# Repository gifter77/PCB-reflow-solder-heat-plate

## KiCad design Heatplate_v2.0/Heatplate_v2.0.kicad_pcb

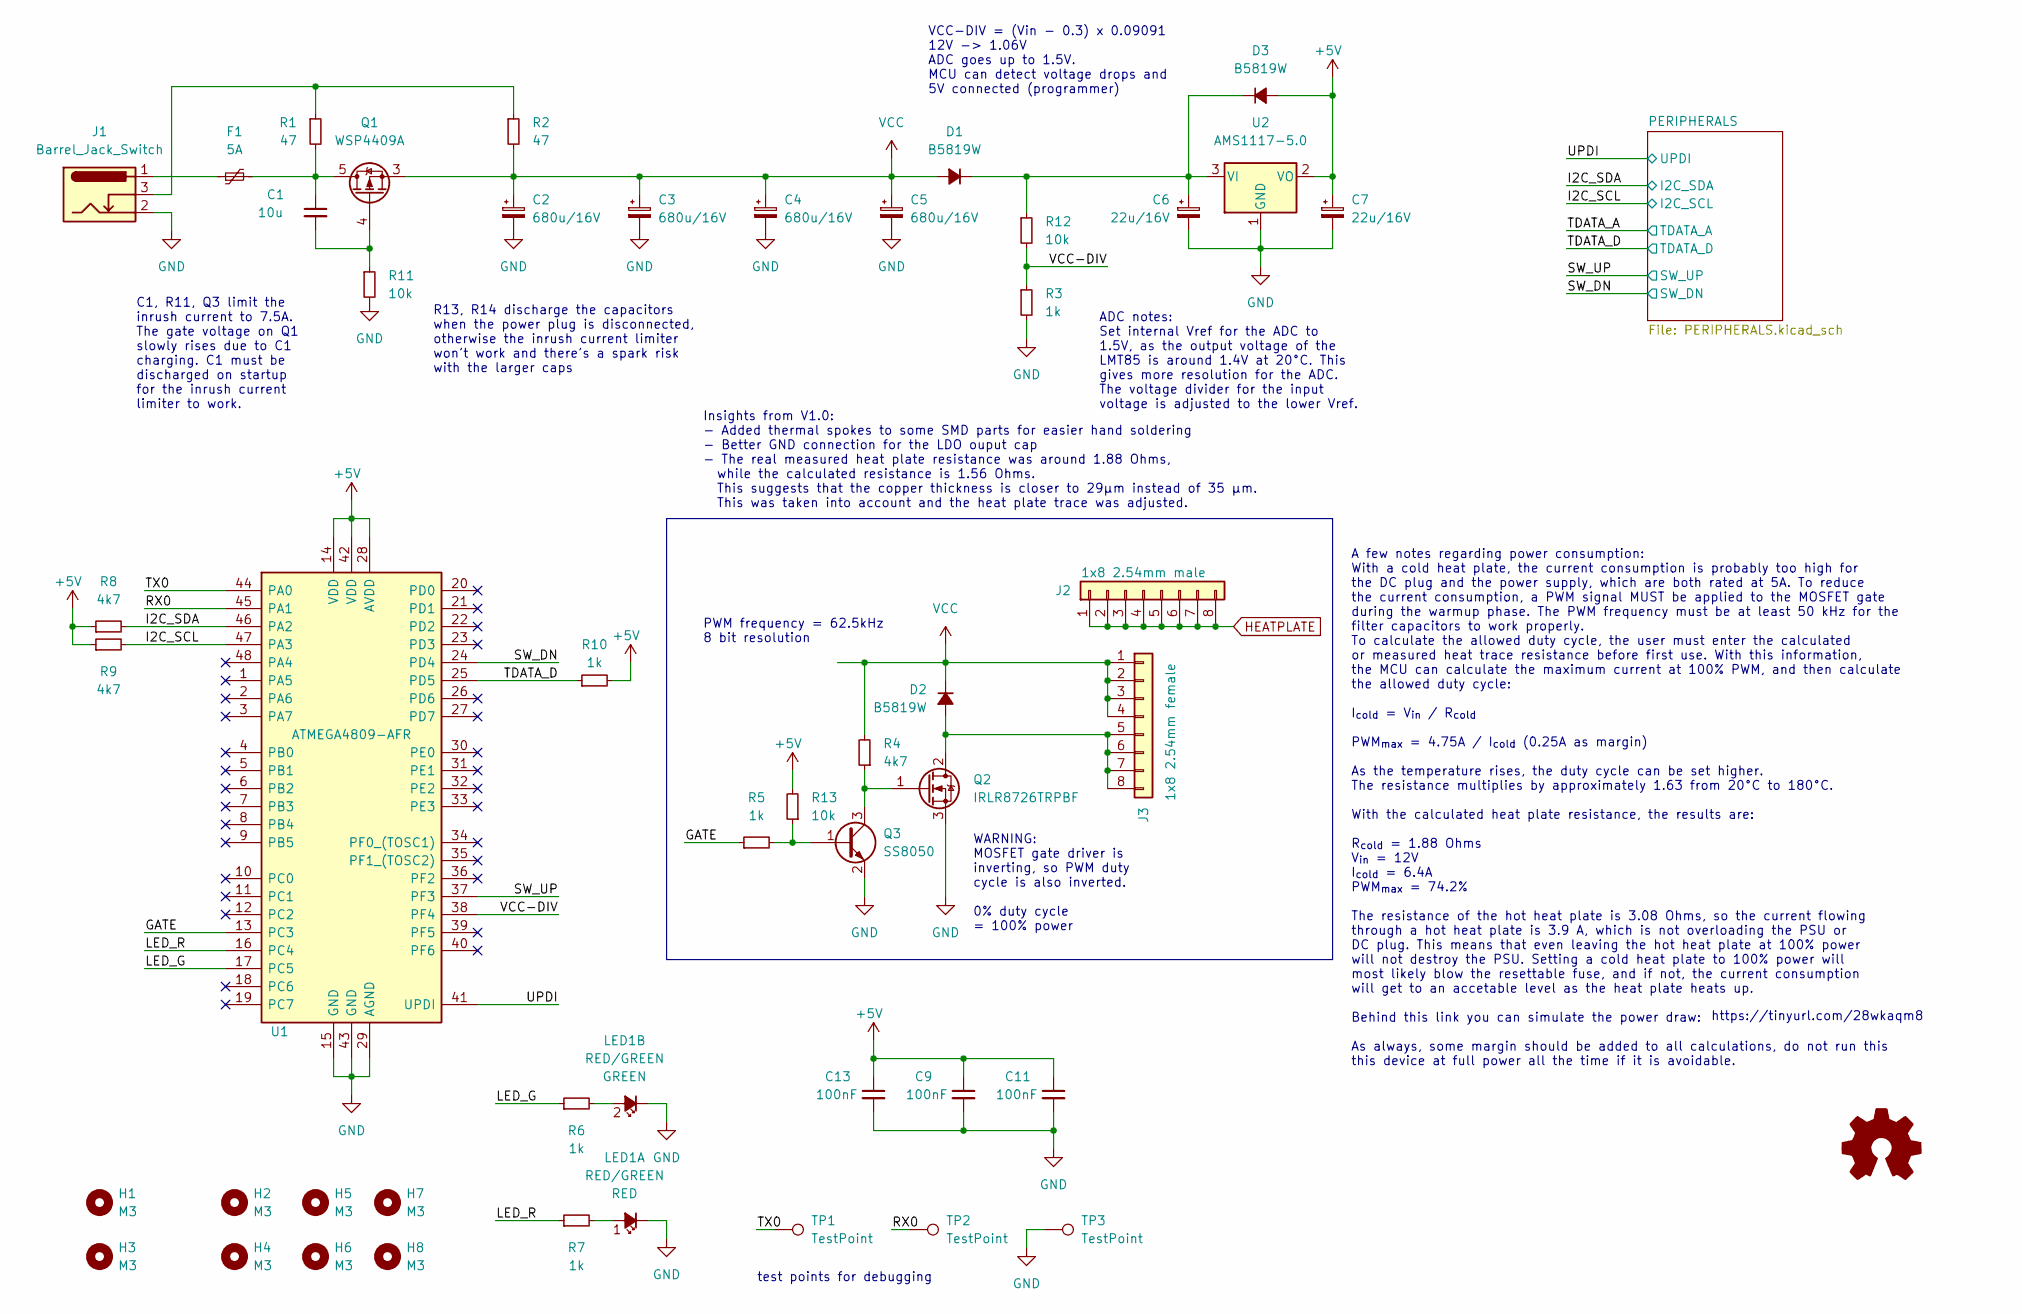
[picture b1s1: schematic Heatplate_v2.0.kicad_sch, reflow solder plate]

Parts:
C1: 10u; C_0805_2012Metric; LCSC Part Number C2922480
C2, C3, C4, C5: 680u/16V; CP_Radial_D8.0mm_P3.50mm; LCSC Part Number C88760
C6, C7: 22u/16V; CP_Elec_4x5.4; LCSC Part Number C88799
C9, C11, C13: 100nF; C_0805_2012Metric; LCSC Part Number C1711
D1, D2, D3: B5819W; D_SOD-123; LCSC Part Number C64885
F1: 5A; Fuse_2920_7451Metric; LCSC Part Number C910846
H1, H2, H3, H4, H5, H6, H7, H8: M3; MountingHole_3.2mm_M3; LCSC Part Number C551332
J1: Barrel_Jack_Switch; BarrelJack_Horizontal; LCSC Part Number C381115
J2: 1x8 2.54mm male; PinHeader_1x08_P2.54mm_Horizontal; LCSC Part Number C2905427
J3: 1x8 2.54mm female; PinSocket_1x08_P2.54mm_Horizontal; LCSC Part Number C2932682
LED1: RED/GREEN; LED_Avago_PLCC4_3.2x2.8mm_CW; LCSC Part Number C131251
LOGO1: Logo_Open_Hardware_Small; OSHW-Logo2_7.3x6mm_SilkScreen
Q1: WSP4409A; SOIC-8_3.9x4.9mm_P1.27mm; LCSC Part Number C2880527
Q2: IRLR8726TRPBF; TO-252-2; LCSC Part Number C81137
Q3: SS8050; SOT-23; LCSC Part Number C444722
R1, R2: 47; R_0805_2012Metric; LCSC Part Number C17714
R3, R5, R6, R7: 1k; R_0805_2012Metric; LCSC Part Number C17513
R4, R8, R9: 4k7; R_0805_2012Metric; LCSC Part Number C17673
R10: 1k; R_0805_2012Metric; LCSC Part Number C17673
R11, R12, R13: 10k; R_0805_2012Metric; LCSC Part Number C17414
TP1, TP2, TP3: TestPoint; TestPoint_Pad_D1.5mm
U1: ATMEGA4809-AFR; TQFP-48_7x7mm_P0.5mm; Manufacturer_Part_Number ATMEGA4809-AFR; Mouser Part Number 556-ATMEGA4809-AFR
U2: AMS1117-5.0; SOT-89-3; LCSC Part Number C351450

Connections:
+5V: C7.1, C9.1, C11.1, C13.1, D3.2 (A), R8.1, R9.1, R10.2, R13.2, U1.14 (VDD), U1.28 (AVDD), U1.42 (VDD), U2.2 (VO); also elsewhere on the board
/GATE: R5.1, U1.13 (PC3)
/I2C_SCL: R9.2, U1.47 (PA3); also elsewhere on the board
/I2C_SDA: R8.2, U1.46 (PA2); also elsewhere on the board
/LED_G: R6.1, U1.17 (PC5)
/LED_R: R7.1, U1.16 (PC4)
/RX0: TP2.1, U1.45 (PA1)
/SW_DN: U1.24 (PD4); also elsewhere on the board
/SW_UP: U1.37 (PF3); also elsewhere on the board
/TDATA_D: R10.1, U1.25 (PD5); also elsewhere on the board
/TX0: TP1.1, U1.44 (PA0)
/UPDI: U1.41 (UPDI); also elsewhere on the board
/VCC-DIV: R3.1, R12.2, U1.38 (PF4)
GND: C2.2, C3.2, C4.2, C5.2, C6.2, C7.2, C9.2, C11.2, C13.2, J1.2, LED1.2 (K1), LED1.4 (K2), Q2.3 (S), Q3.2 (E), R3.2, R11.2, TP3.1, U1.15 (GND), U1.29 (AGND), U1.43 (GND), U2.1 (GND); also elsewhere on the board
unnamed: C1.1, F1.2, Q1.5 (D), Q1.6 (D), Q1.7 (D), Q1.8 (D), R1.2
unnamed: C6.1, D1.1 (K), D3.1 (K), R12.1, U2.3 (VI)
unnamed 17: D2.2 (A), Q2.2 (D); also elsewhere on the board
unnamed: F1.1, J1.1
unnamed: J1.3, R1.1, R2.1
unnamed: LED1.1 (A1), R7.2
unnamed: LED1.3 (A2), R6.2
unnamed: C1.2, Q1.4 (G), R11.1
unnamed: Q2.1 (G), Q3.3 (C), R4.1
unnamed: Q3.1 (B), R5.2, R13.1
VCC: C2.1, C3.1, C4.1, C5.1, D1.2 (A), D2.1 (K), Q1.1 (S), Q1.2 (S), Q1.3 (S), R2.2, R4.2; also elsewhere on the board

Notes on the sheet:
C1, R11, Q3 limit the inrush current to 7.5A. The gate voltage on Q1 slowly rises due to C1 charging. C1 must be discharged on startup for the inrush current limiter to work.
VCC-DIV = (Vin - 0.3) x 0.09091 12V -> 1.06V ADC goes up to 1.5V. MCU can detect voltage drops and 5V connected (programmer)
PWM frequency = 62.5kHz 8 bit resolution
A few notes regarding power consumption: With a cold heat plate, the current consumption is probably too high for the DC plug and the power supply, which are both rated at 5A. To reduce the current consumption, a PWM signal MUST be applied to the MOSFET gate during the warmup phase. The PWM frequen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
WARNING: MOSFET gate driver is inverting, so PWM duty cycle is also inverted. 0% duty cycle = 100% power
R13, R14 discharge the capacitors when the power plug is disconnected, otherwise the inrush current limiter won't work and there's a spark risk with the larger caps
https://tinyurl.com/28wkaqm8
test points for debugging
ADC notes: Set internal Vref for the ADC to 1.5V, as the output voltage of the LMT85 is around 1.4V at 20°C. This gives more resolution for the ADC. The voltage divider for the input voltage is adjusted to the lower Vref.
Insights from V1.0: - Added thermal spokes to some SMD parts for easier hand soldering - Better GND connection for the LDO ouput cap - The real measured heat plate resistance was around 1.88 Ohms, while the calculated resistance is 1.56 Ohms. This suggests that the copper thickness is closer to 29µ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

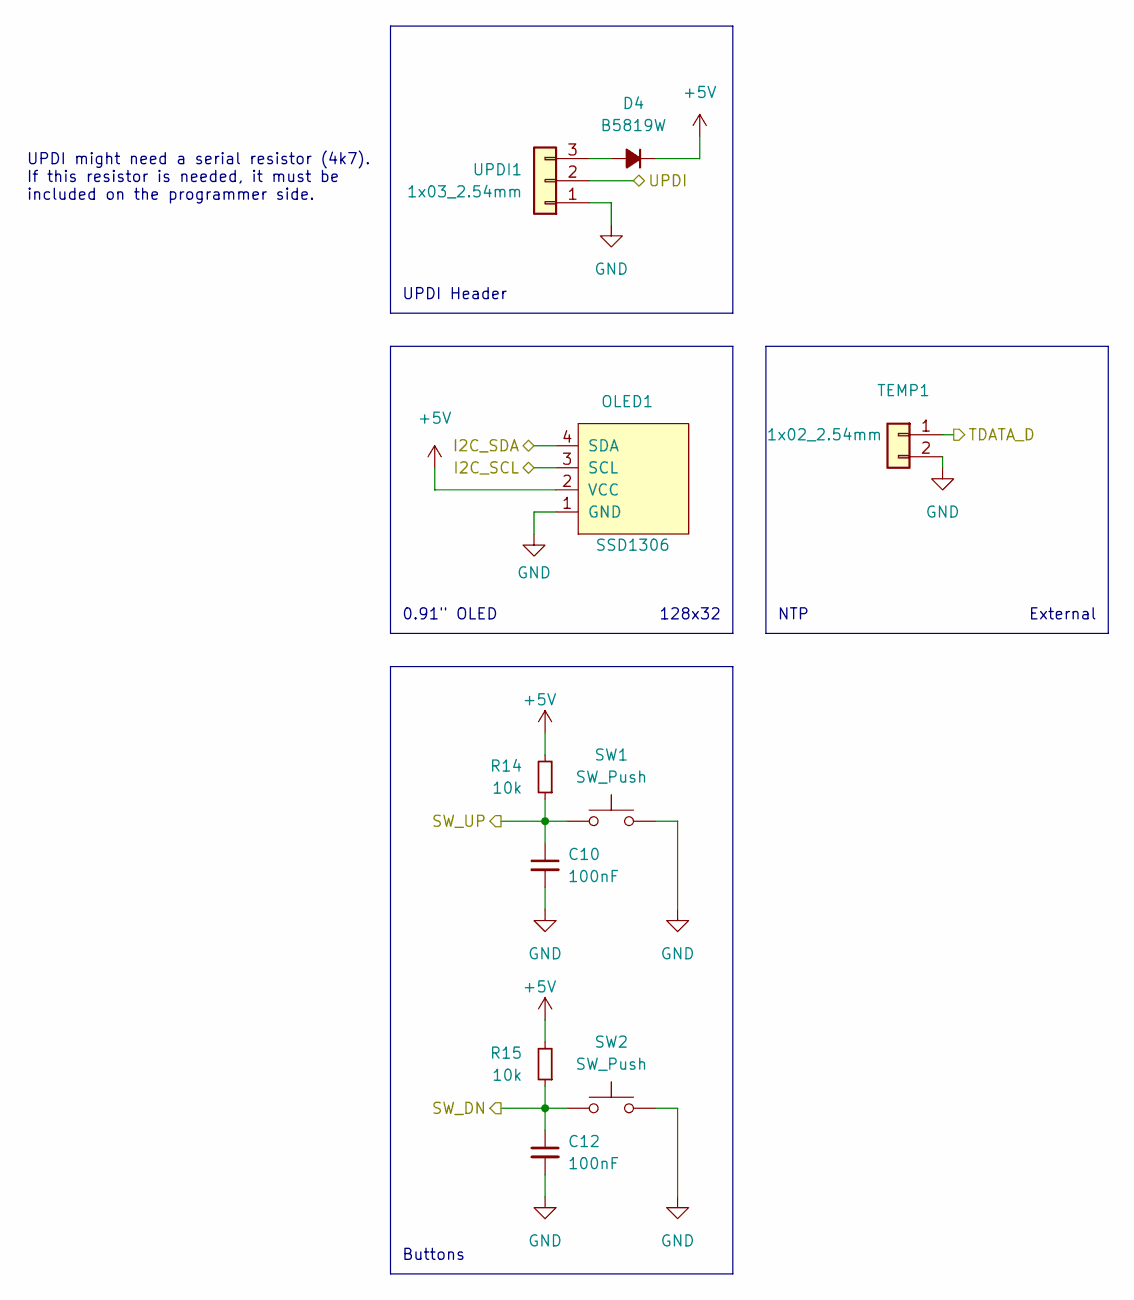
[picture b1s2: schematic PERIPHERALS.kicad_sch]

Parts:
C10, C12: 100nF; C_0805_2012Metric; LCSC Part Number C1711
D4: B5819W; D_SOD-123; LCSC Part Number C64885
OLED1: SSD1306; 0.91Inch-OLED-Module; LCSC Part Number C2718488
R14, R15: 10k; R_0805_2012Metric; LCSC Part Number C17414
SW1, SW2: SW_Push; SW_PUSH_6mm; LCSC Part Number C136682
TEMP1: 1x02_2.54mm; PinHeader_1x02_P2.54mm_Vertical; LCSC Part Number C2905434
UPDI1: 1x03_2.54mm; PinHeader_1x03_P2.54mm_Vertical; LCSC Part Number C49257

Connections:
+5V: D4.1 (K), OLED1.2 (VCC), R14.2, R15.2; also elsewhere on the board
/I2C_SCL: OLED1.3 (SCL); also elsewhere on the board
/I2C_SDA: OLED1.4 (SDA); also elsewhere on the board
/SW_DN: C12.1, R15.1, SW2.1; also elsewhere on the board
/SW_UP: C10.1, R14.1, SW1.1; also elsewhere on the board
/TDATA_D: TEMP1.1; also elsewhere on the board
/UPDI: UPDI1.2; also elsewhere on the board
GND: C10.2, C12.2, OLED1.1 (GND), SW1.2, SW2.2, TEMP1.2, UPDI1.1; also elsewhere on the board
unnamed: D4.2 (A), UPDI1.3

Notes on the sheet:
NTP
UPDI Header
128x32
0.91" OLED
Buttons
UPDI might need a serial resistor (4k7). If this resistor is needed, it must be included on the programmer side.
External

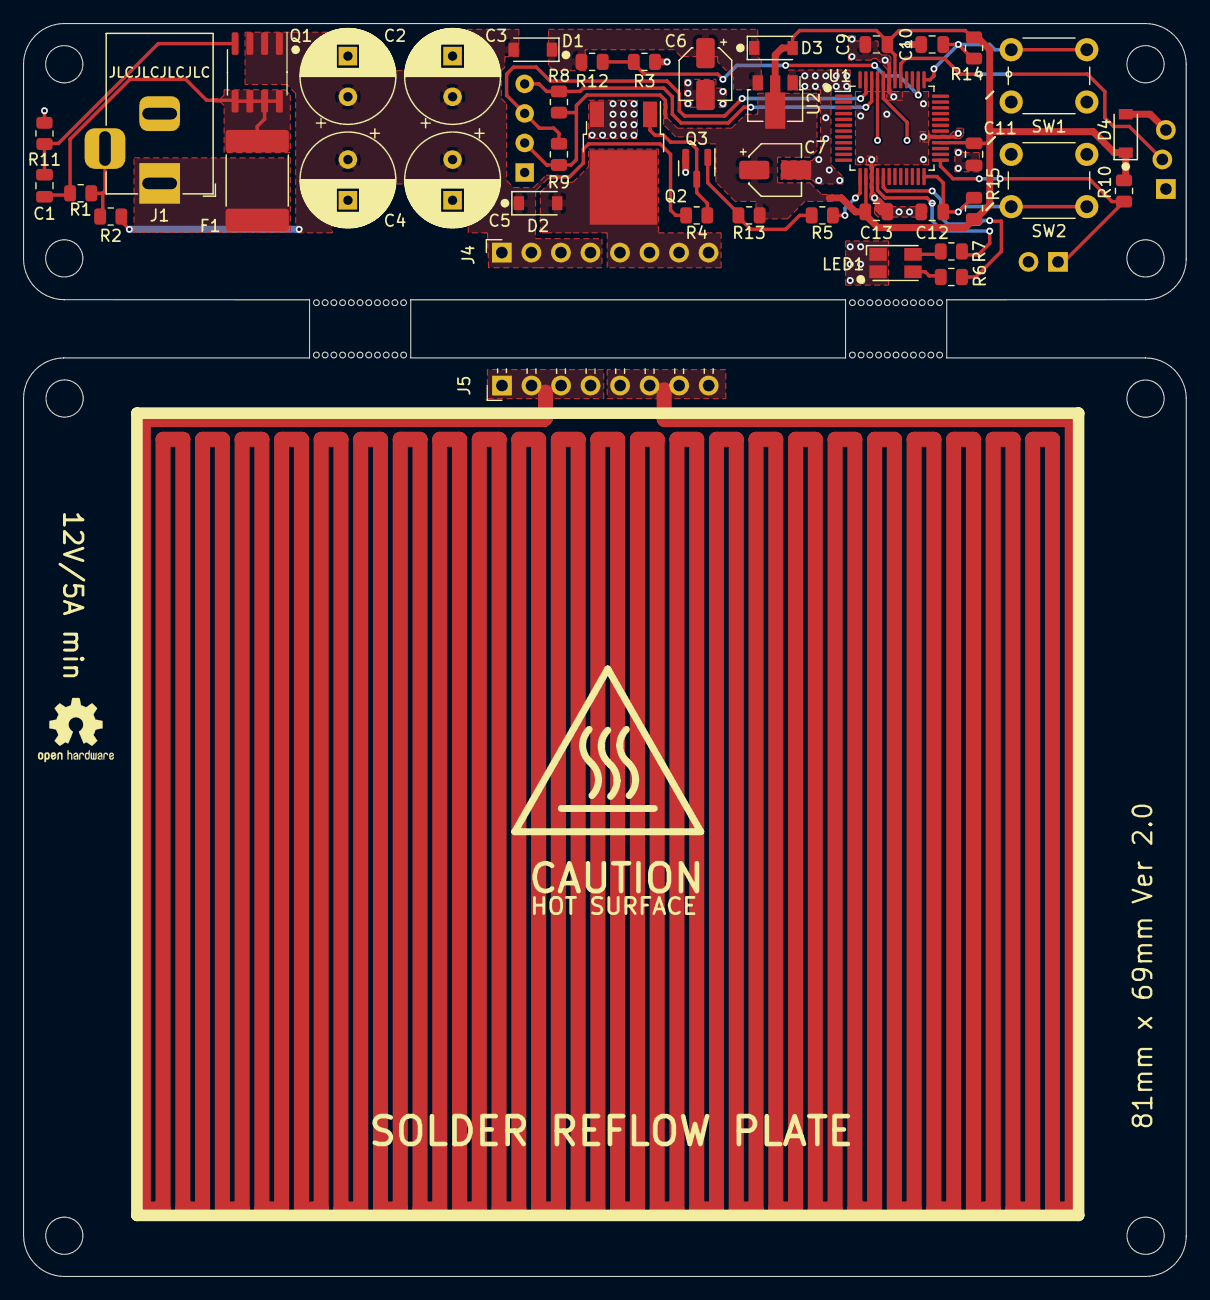
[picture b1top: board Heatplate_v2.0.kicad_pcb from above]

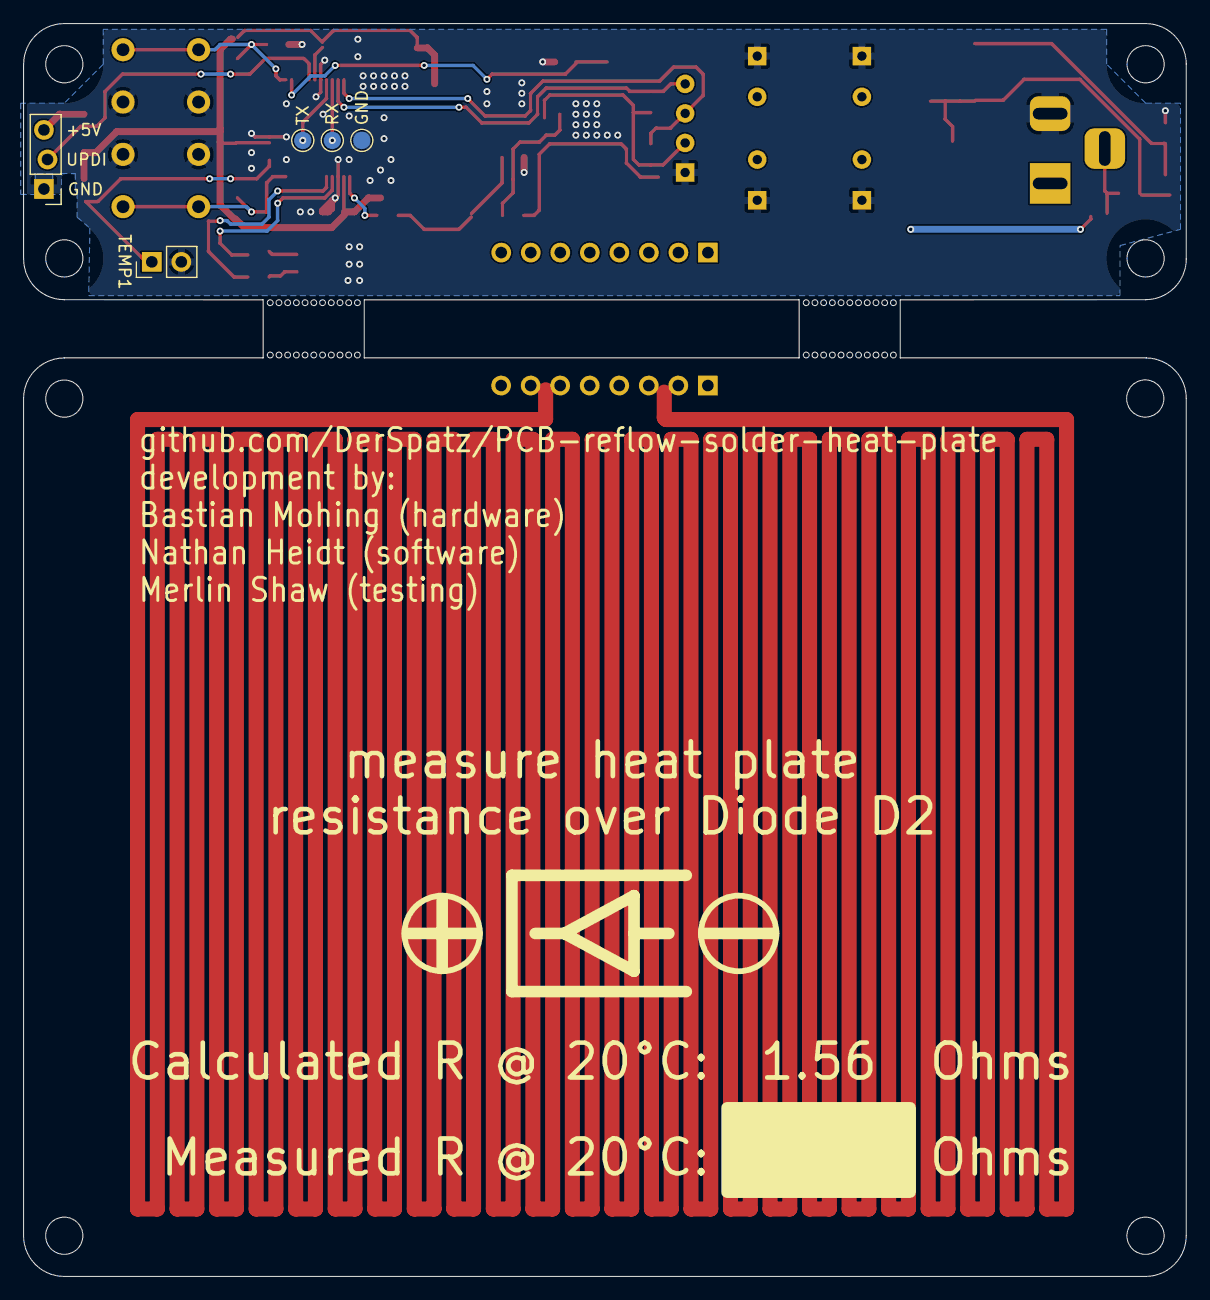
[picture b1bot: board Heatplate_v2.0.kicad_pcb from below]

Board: 2 copper layers, 100.0 x 107.8 mm, 60 parts (5 on the bottom side), 27 nets.

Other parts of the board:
J4: 1x8 2.54mm female; PinSocket_1x08_P2.54mm_Horizontal
J5: 1x8 2.54mm male; PinHeader_1x08_P2.54mm_Horizontal
mouse-bite-5mm-slot, mouse-bite-5mm-slot#2: VAL**; mouse-bite-5mm-slot

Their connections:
HEATPLATE: J5.1, J5.2, J5.3, J5.4, J5.5, J5.6, J5.7, J5.8
unnamed 17: J4.5, J4.6, J4.7, J4.8; also elsewhere on the board
VCC: J4.1, J4.2, J4.3, J4.4; also elsewhere on the board

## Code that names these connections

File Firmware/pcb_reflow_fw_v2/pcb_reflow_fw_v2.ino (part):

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Adafruit_SSD1306 display(SCREEN_WIDTH, SCREEN_HEIGHT, &Wire, -1); // Create Display

// Pin Definitions
#define MOSFET_PIN PIN_PC3
#define UPSW_PIN PIN_PF3
#define DNSW_PIN PIN_PD4
#define TEMP_PIN PIN_PD5 //PIN_PF2 // A2
#define VCC_PIN PIN_PF4  // A0
#define LED_GREEN_PIN PIN_PC5
#define LED_RED_PIN PIN_PC4
//#define ONE_WIRE_BUS PIN_PD5

#define MOSFET_PIN_OFF 255

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
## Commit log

2023-03-21 Modified code to use NTC thermistor
2023-04-10 Split PCB and heat plate
2023-04-24 Minor fixes
2023-04-24 Revert "Modified code to use NTC thermistor"
    This reverts commit af9c8fac893489ef4b004f58479b9359fe9118f5.
2023-04-24 NTC thermistor and PID auto-tuning firmware moved into separate v2 directory
2023-04-24 Squashed commit of the following:
    commit 8e63c85fbbaf13759d6261f9b10b379e95262986
    Author: gifter77 <17034102+gifter77@users.noreply.github.com>
    Date: Mon Apr 24 12:47:02 2023 +0100
    NTC thermistor and PID auto-tuning firmware moved into separate v2 directory
    commit 072c7ec0e5f50c28c2462603dc7d94ad727fff54
    Author: gifter77 <17034102+gifter77@users.noreply.github.com>
